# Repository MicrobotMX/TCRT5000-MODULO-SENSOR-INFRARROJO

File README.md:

TCRT5000 - MÓDULO SENSOR INFRARROJO
==================================
Drescripción
------------
Este módulo es utilizado para la detección del color blanco y negro en los robots seguidores de línea, encoders y como interruptor de límite en aplicaciones mecánicas. Está basado en el sensor infrarrojo TCRT5000 con filtro de luz ambiental y una distancia de detección mayor que otros sensores como el CNY70 o QRD1114. Cuenta con un pequeño potenciómetro que te permite ajustar la distancia de detección. 

Contenido
--------
Archivos de diseño en [EAGLE](https://www.autodesk.com/products/eagle/free-download):
- Esquemático(.sch)
- PCB(.brd).

Más información
---------------
Página del producto:
-	https://www.microbot.mx/products/tcrt5000-modulo-sensor-infrarrojo

Licencia
--------
Este producto es hardware libre bajo la licencia [Creative Commons Share-alike 4.0 International](https://creativecommons.org/licenses/by-sa/4.0/). Es libre de copiar, redistribuir y modificar, siempre que otorgue crédito a los autores y comparta sus contribuciones bajo la misma licencia.

*El Equipo de Microbot*

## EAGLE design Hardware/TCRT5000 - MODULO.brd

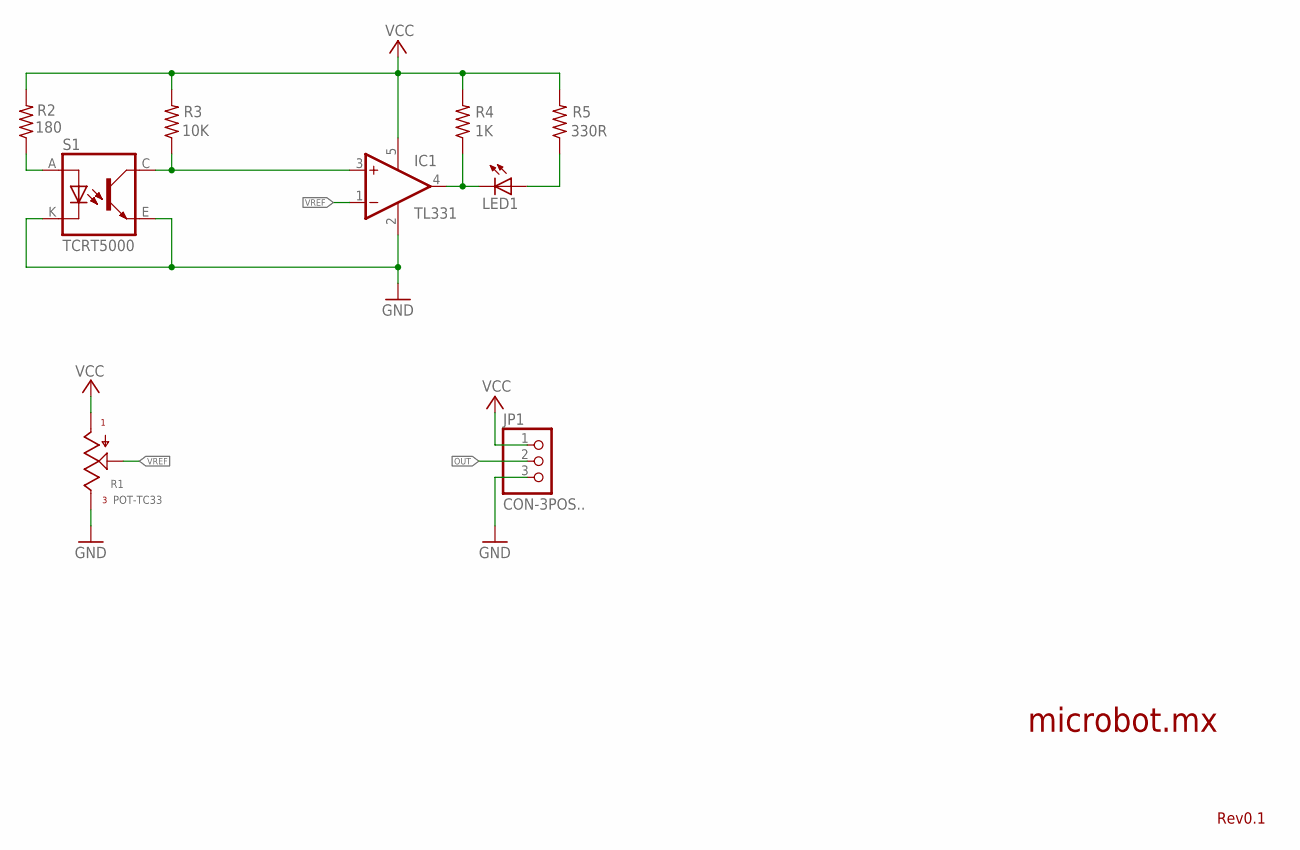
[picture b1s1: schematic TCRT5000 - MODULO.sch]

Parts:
IC1: TL331; DBV-R-PDSO-G5
JP1: CON-3POS..; 1X03-GND
LED1: LEDCHIPLED_1206; CHIPLED_1206
R1: POT-TC33; TC33
R2: 180; R1206
R3: 10K; R1206
R4: 1K; R1206
R5: 330R; R1206
S1: TCRT5000

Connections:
GND: IC1.2 (GND), JP1.3, R1.3, S1.E (EMISOR), S1.K (CÁTODO)
unnamed: R2.1, S1.A (ÁNODO)
unnamed: IC1.3 (+IN), R3.1, S1.C (COLECTOR)
unnamed: LED1.A, R5.1
OUT: IC1.4 (OUT), JP1.2, LED1.C, R4.1
VCC: IC1.5 (V+), JP1.1, R1.1, R2.2, R3.2, R4.2, R5.2
VREF: IC1.1 (-IN), R1.2

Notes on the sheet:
Rev0.1
microbot.mx

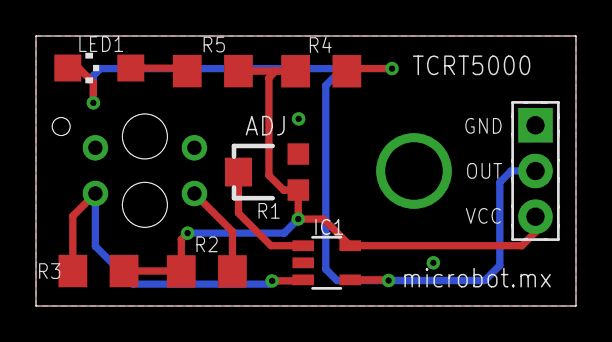
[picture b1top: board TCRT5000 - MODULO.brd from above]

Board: 2 copper layers, 30.0 x 15.0 mm, 9 parts (1 on the bottom side), 7 nets.
